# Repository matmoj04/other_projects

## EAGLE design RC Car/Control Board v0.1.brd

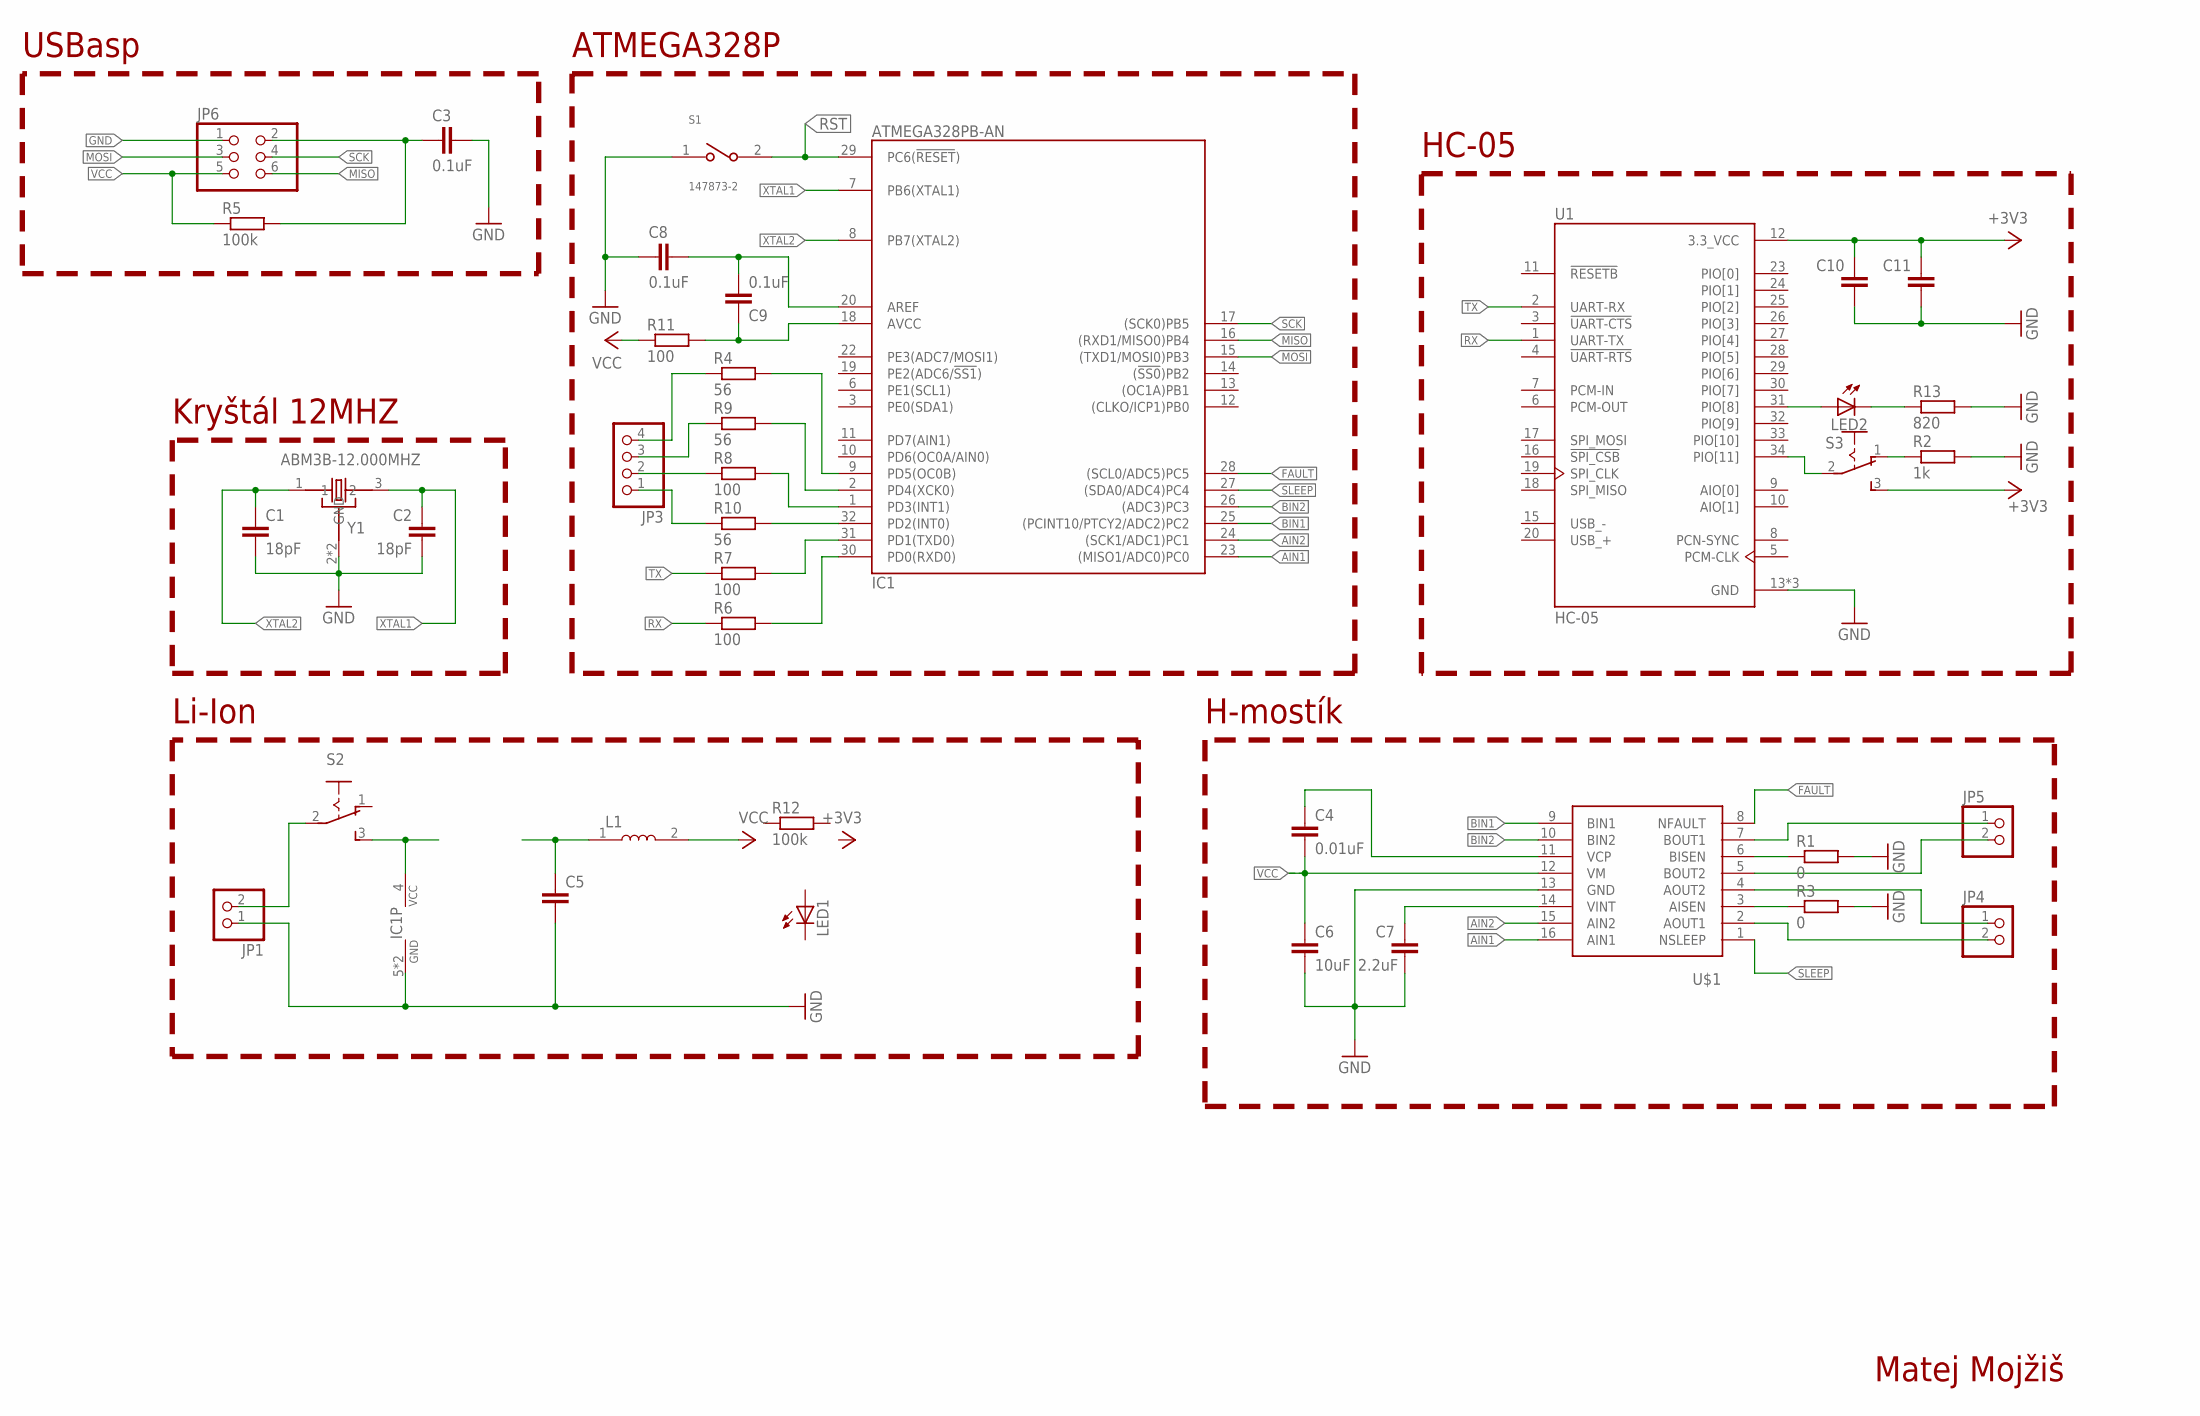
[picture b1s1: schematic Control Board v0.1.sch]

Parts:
C1, C2: 18pF; C0805
C3, C8, C9: 0.1uF; C0805
C4: 0.01uF; C0805
C5, C10, C11: C-EUC0805; C0805
C6: 10uF; C0805
C7: 2.2uF; C0805
IC1: ATMEGA328PB-AN; QFP32_7X7_0.80
JP1, JP4, JP5: PINHD-1X2/90; 1X02/90
JP3: PINHD-1X4; 1X04
JP6: PINHD-2X3; 2X03
L1: MLF2012C330KT000; INDC2012X87N
LED1, LED2: LEDCHIPLED_0805; CHIPLED_0805
R1, R3: 0; R0805
R2: 1k; R0805
R4, R9, R10: 56; R0805
R5, R12: 100k; R0805
R6, R7, R8, R11: 100; R0805
R13: 820; R0805
S1: 147873-2; SW_147873-2
S2: 255SB
S3: M251
U1: HC-05; XCVR_HC-05
U$1: DVR8833SUPERFICIAL; PWP16
Y1: ABM3B-12.000MHZ; OSCSC500X320X110-4N

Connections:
+3V3: C10.1, C11.1, S3.3 (S), U1.12 (3.3_VCC)
AIN1: IC1.23 ((MISO1/ADC0)PC0), U$1.16 (AIN1)
AIN2: IC1.24 ((SCK1/ADC1)PC1), U$1.15 (AIN2)
BIN1: IC1.25 ((PCINT10/PTCY2/ADC2)PC2), U$1.9 (BIN1)
BIN2: IC1.26 ((ADC3)PC3), U$1.10 (BIN2)
FAULT: IC1.28 ((SCL0/ADC5)PC5), U$1.8 (NFAULT)
GND: C1.2, C2.2, C3.1, C5.2, C6.2, C7.2, C8.2, C10.2, C11.2, IC1.5 (GND), IC1.21 (GND), JP1.1, JP6.1, R1.2, R2.2, R3.2, R13.2, S1.1, U1.13 (GND), U1.21 (GND), U1.22 (GND), U$1.13 (GND), Y1.2 (GND), Y1.4 (GND)
MISO: IC1.16 ((RXD1/MISO0)PB4), JP6.6
MOSI: IC1.15 ((TXD1/MOSI0)PB3), JP6.3
unnamed: IC1.4 (VCC), S2.3 (S)
unnamed: IC1.31 (PD1(TXD0)), R7.2
unnamed: JP1.2, S2.2
unnamed: JP5.1, U$1.7 (BOUT1)
unnamed: IC1.30 (PD0(RXD0)), R6.2
unnamed: IC1.32 (PD2(INT0)), R10.2
unnamed: JP5.2, U$1.5 (BOUT2)
unnamed: JP4.1, U$1.4 (AOUT2)
unnamed: JP4.2, U$1.2 (AOUT1)
unnamed: R1.1, U$1.6 (BISEN)
unnamed: R3.1, U$1.3 (AISEN)
unnamed: LED2.A, U1.31 (PIO[8])
unnamed: C4.1, U$1.11 (VCP)
unnamed: LED2.C, R13.1
unnamed: C7.1, U$1.14 (VINT)
unnamed: IC1.1 (PD3(INT1)), R8.2
unnamed: S3.2, U1.34 (PIO[11])
unnamed: R2.1, S3.1 (O)
unnamed: C5.1, L1.1
unnamed: IC1.2 (PD4(XCK0)), R9.2
unnamed: IC1.9 (PD5(OC0B)), R4.2
unnamed: JP3.4, R4.1
unnamed: JP3.1, R10.1
unnamed: JP3.2, R8.1
unnamed: JP3.3, R9.1
unnamed: C8.1, C9.2, IC1.20 (AREF)
unnamed: C9.1, IC1.18 (AVCC), R11.2
RST: C3.2, IC1.29 (PC6(!RESET!)), JP6.2, R5.2, S1.2
RX: R6.1, U1.1 (UART-TX)
SCK: IC1.17 ((SCK0)PB5), JP6.4
SLEEP: IC1.27 ((SDA0/ADC4)PC4), U$1.1 (NSLEEP)
TX: R7.1, U1.2 (UART-RX)
VCC: C4.2, C6.1, JP6.5, L1.2, R5.1, R11.1, U$1.12 (VM)
XTAL1: C2.1, IC1.7 (PB6(XTAL1)), Y1.3 (2)
XTAL2: C1.1, IC1.8 (PB7(XTAL2)), Y1.1

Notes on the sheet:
Li-Ion
USBasp
H-mostík
Kryštál 12MHZ
ATMEGA328P
HC-05
Matej Mojžiš

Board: 2 copper layers, 39 parts (0 on the bottom side), 44 nets, no tracks yet.

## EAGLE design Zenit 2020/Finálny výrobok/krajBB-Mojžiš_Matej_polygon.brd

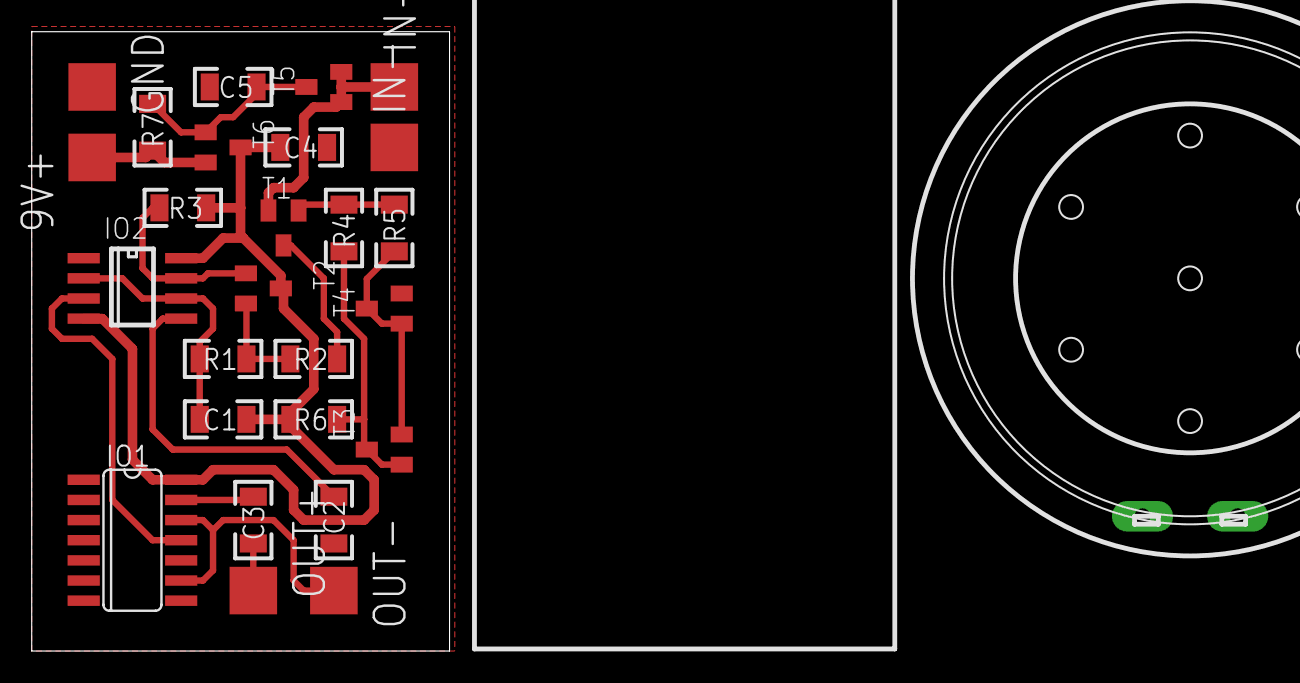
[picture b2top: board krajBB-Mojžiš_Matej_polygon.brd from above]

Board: 2 copper layers, 26.3 x 39.0 mm, 28 parts (0 on the bottom side), 17 nets.

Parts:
9V+: SMD3X3
C1, C2, C3, C4, C5: 1u; 1206
GND: SMD3X3
IN+: SMD3X3
IN-: SMD3X3
IO1: 4013D; SO14
IO2: NE555D; SO08
OUT+: SMD3X3
OUT-: SMD3X3
R1: 100; 1206
R2: 470; 1206
R3, R4: 10k; 1206
R5: 2.2k; 1206
R6: 47k; 1206
R7: 10M; 1206
REPRODUKTOR: LD-DR-3519
T1, T2, T3, T4: BC817-25; SOT23-BEC
T5, T6: BSS84; SOT23
U$1: 9VBATTERY

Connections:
9V_1: R4.2, R6.1, T3.B, T3.C
9V_2: R5.1, T3.E, T4.B, T4.C
+9V: C1.2, C4.2, IO1.14, IO2.4, IO2.8, R3.2, R6.2, T2.C, T6.3
CLOCK: IO1.11, IO2.3
CV: C2.2, IO2.5
DIS: IO2.7, R3.1, T2.B
DIS_1: R2.1, T1.C
DIS_IN: R1.1, R2.2, T2.E
DIV: R4.1, R5.2, T1.B
GND: C2.1, C4.1, C5.1, GND.P$1, IN-.P$1, IO1.7, IO1.8, IO1.10, IO2.1, T4.E
IN: IN+.P$1, T1.E, T5.1, T5.2
MOS: C5.2, R7.1, T5.3, T6.1
OUT: C3.1, IO1.13
REP: C3.2, OUT+.P$1
REP+: IO1.9, IO1.12, OUT-.P$1
THR: C1.1, IO2.2, IO2.6, R1.2
VIN: 9V+.P$1, R7.2, T6.2
